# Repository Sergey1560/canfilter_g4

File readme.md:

# CAN Filter

[Схема платы](./canfilter_g4.pdf)

# Примеры кода

- [AEM2ABIT](https://github.com/Sergey1560/canfilter_aem2abit) конвертирует сообщения от ШДК AEM в формат ADLM ABIT
- [SOCKET_CAN](https://github.com/Sergey1560/canfilter_socketcan_sw) USB адаптер для Linux с 3-мя интерфейсами CAN

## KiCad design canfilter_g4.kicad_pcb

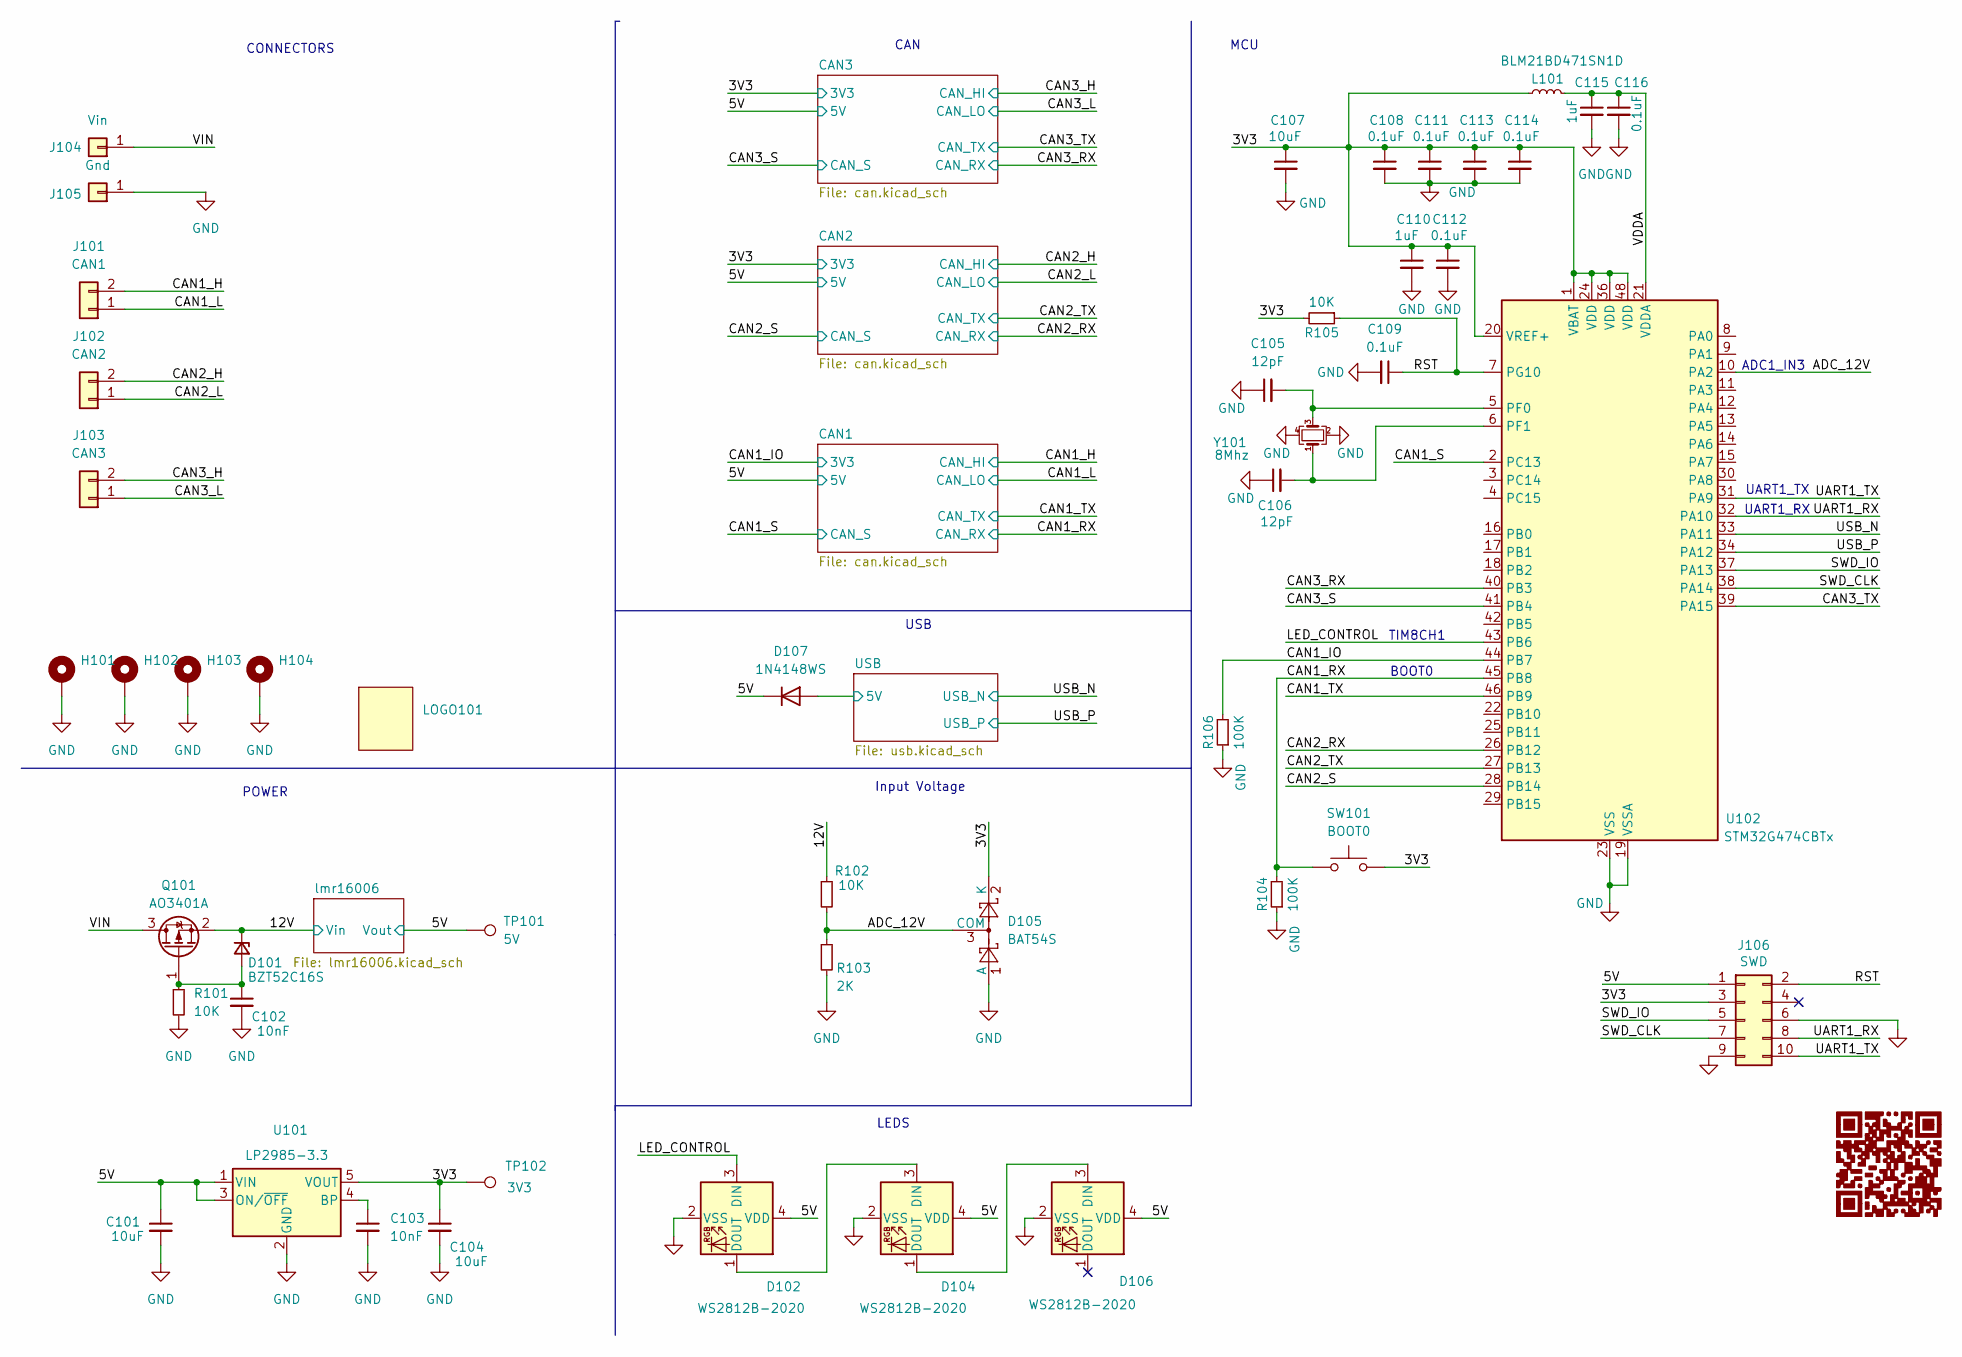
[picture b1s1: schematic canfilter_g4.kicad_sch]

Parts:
C101: 10uF; C_1206_3216Metric; LCSC C91186
C102, C103: 10nF; C_0603_1608Metric; LCSC C100042
C104: 10uF; C_1206_3216Metric; LCSC C162273
C105, C106: 12pF; C_0603_1608Metric; LCSC C519482
C107: 10uF; C_1206_3216Metric; LCSC C91606
C108, C109, C111, C113, C114, C116: 0.1uF; C_0603_1608Metric; LCSC C92490
C110: 1uF; C_0805_2012Metric; LCSC C91186
C112: 0.1uF; C_0805_2012Metric; LCSC C92490
C115: 1uF; C_0805_2012Metric; LCSC C91185
D101: BZT52C16S; D_SOD-323; LCSC C19077449
D102, D104, D106: WS2812B-2020; LED_WS2812B-2020_PLCC4_2.0x2.0mm; LCSC C965555
D105: BAT54S; SOT-23; LCSC C5805802
D107: 1N4148WS; D_SOD-323
H101, H102, H103, H104: MountingHole_3.2mm_M3_Pad_Via
J101: CAN1; PinHeader_1x02_P2.54mm_Vertical
J102: CAN2; PinHeader_1x02_P2.54mm_Vertical
J103: CAN3; PinHeader_1x02_P2.54mm_Vertical
J104: Vin; PinHeader_1x01_P2.54mm_Vertical
J105: Gnd; PinHeader_1x01_P2.54mm_Vertical
J106: SWD; PinHeader_2x05_P1.27mm_Vertical_SMD; LCSC C42372555
L101: BLM21BD471SN1D; L_0805_2012Metric; LCSC C710507
LOGO101: logo_15x9
Q101: AO3401A; SOT-23; LCSC C347476
R101, R102, R105: 10K; R_0603_1608Metric; LCSC C98220
R103: 2K; R_0603_1608Metric; LCSC C125933
R104, R106: 100K; R_0603_1608Metric; LCSC C98220
SW101: BOOT0; SW_Push_SPST_NO_Alps_SKRK
TP101: 5V; TestPoint_Pad_1.0x1.0mm
TP102: 3V3; TestPoint_Pad_1.0x1.0mm
U101: LP2985-3.3; SOT-23-5; LCSC C95414
U102: STM32G474CBTx; LQFP-48_7x7mm_P0.5mm; LCSC C730123
Y101: 8Mhz; Crystal_SMD_3225-4Pin_3.2x2.5mm; LCSC C2682775

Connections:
/3V3: C104.1, C107.1, C108.1, C110.1, C111.1, C112.1, C113.1, C114.1, D105.2 (K), J106.3, L101.1, R105.2, SW101.2, TP102.1, U101.5 (VOUT), U102.1 (VBAT), U102.20 (VREF+), U102.24 (VDD), U102.36 (VDD), U102.48 (VDD); also elsewhere on the board
/5V: C101.1, D102.4 (VDD), D104.4 (VDD), D106.4 (VDD), D107.1 (K), J106.1, TP101.1, U101.1 (VIN), U101.3 (ON/~OFF); also elsewhere on the board
/12V: D101.1 (K), Q101.2 (S), R102.1; also elsewhere on the board
/ADC_12V: D105.3 (COM), R102.2, R103.1, U102.10 (PA2)
/CAN1_H: J101.2; also elsewhere on the board
/CAN1_IO: R106.2, U102.44 (PB7); also elsewhere on the board
/CAN1_L: J101.1; also elsewhere on the board
/CAN1_RX: R104.2, SW101.1, U102.45 (PB8); also elsewhere on the board
/CAN1_S: U102.2 (PC13); also elsewhere on the board
/CAN1_TX: U102.46 (PB9); also elsewhere on the board
/CAN2_H: J102.2; also elsewhere on the board
/CAN2_L: J102.1; also elsewhere on the board
/CAN2_RX: U102.26 (PB12); also elsewhere on the board
/CAN2_S: U102.28 (PB14); also elsewhere on the board
/CAN2_TX: U102.27 (PB13); also elsewhere on the board
/CAN3_H: J103.2; also elsewhere on the board
/CAN3_L: J103.1; also elsewhere on the board
/CAN3_RX: U102.40 (PB3); also elsewhere on the board
/CAN3_S: U102.41 (PB4); also elsewhere on the board
/CAN3_TX: U102.39 (PA15); also elsewhere on the board
/LED_CONTROL: D102.3 (DIN), U102.43 (PB6)
/RST: C109.1, J106.2, R105.1, U102.7 (PG10)
/SWD_CLK: J106.7, U102.38 (PA14)
/SWD_IO: J106.5, U102.37 (PA13)
/UART1_RX: J106.8, U102.32 (PA10)
/UART1_TX: J106.10, U102.31 (PA9)
/USB/5V: D107.2 (A); also elsewhere on the board
/USB_N: U102.33 (PA11); also elsewhere on the board
/USB_P: U102.34 (PA12); also elsewhere on the board
/VDDA: C115.1, C116.1, L101.2, U102.21 (VDDA)
/VIN: J104.1, Q101.3 (D)
GND: C101.2, C102.2, C103.2, C104.2, C105.1, C106.1, C107.2, C108.2, C109.2, C110.2, C111.2, C112.2, C113.2, C114.2, C115.2, C116.2, D102.2 (VSS), D104.2 (VSS), D105.1 (A), D106.2 (VSS), H101.1, H102.1, H103.1, H104.1, J105.1, J106.6, J106.9, R101.2, R103.2, R104.1, R106.1, U101.2 (GND), U102.19 (VSSA), U102.23 (VSS), U102.35 (VSS), U102.47 (VSS), Y101.2, Y101.4; also elsewhere on the board
unnamed: C102.1, D101.2 (A), Q101.1 (G), R101.1
unnamed: D102.1 (DOUT), D104.3 (DIN)
unnamed: D104.1 (DOUT), D106.3 (DIN)
unnamed: C103.1, U101.4 (BP)
unnamed: C105.2, U102.5 (PF0), Y101.3
unnamed: C106.2, U102.6 (PF1), Y101.1

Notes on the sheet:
POWER
BOOT0
CAN
CONNECTORS
ADC1_IN3
LEDS
UART1_TX
Input Voltage
TIM8CH1
MCU
USB
UART1_RX

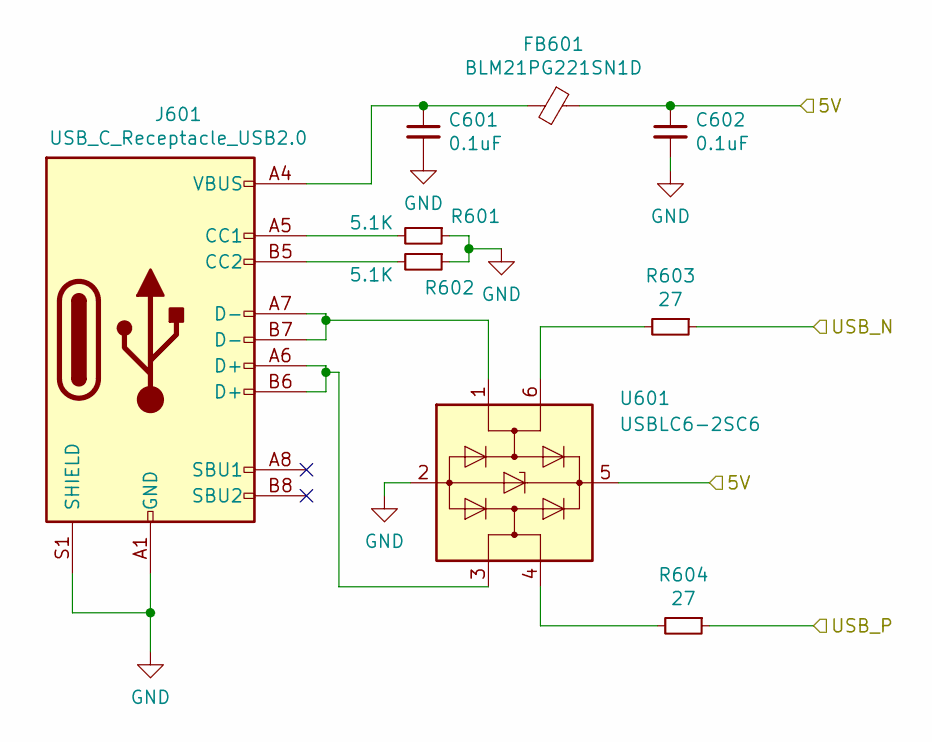
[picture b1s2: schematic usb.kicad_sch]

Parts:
C601, C602: 0.1uF; C_0603_1608Metric
FB601: BLM21PG221SN1D; L_0805_2012Metric
J601: USB_C_Receptacle_USB2.0; USB_C_Receptacle_XKB_U262-16XN-4BVC11
R601, R602: 5.1K; R_0603_1608Metric
R603, R604: 27; R_0603_1608Metric
U601: USBLC6-2SC6; SOT-23-6; LCSC C7519

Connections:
/USB/5V: C602.1, FB601.1, U601.5 (VBUS); also elsewhere on the board
/USB_N: R603.1; also elsewhere on the board
/USB_P: R604.1; also elsewhere on the board
GND: C601.2, C602.2, J601.A1 (GND), J601.A12 (GND), J601.B1 (GND), J601.B12 (GND), J601.S1 (SHIELD), R601.1, R602.1, U601.2 (GND); also elsewhere on the board
unnamed: C601.1, FB601.2, J601.A4 (VBUS), J601.A9 (VBUS), J601.B4 (VBUS), J601.B9 (VBUS)
unnamed: J601.A5 (CC1), R601.2
unnamed: J601.B5 (CC2), R602.2
unnamed: J601.A6 (D+), J601.B6 (D+), U601.3 (I/O2)
unnamed: J601.A7 (D-), J601.B7 (D-), U601.1 (I/O1)
unnamed: R603.2, U601.6 (I/O1)
unnamed: R604.2, U601.4 (I/O2)

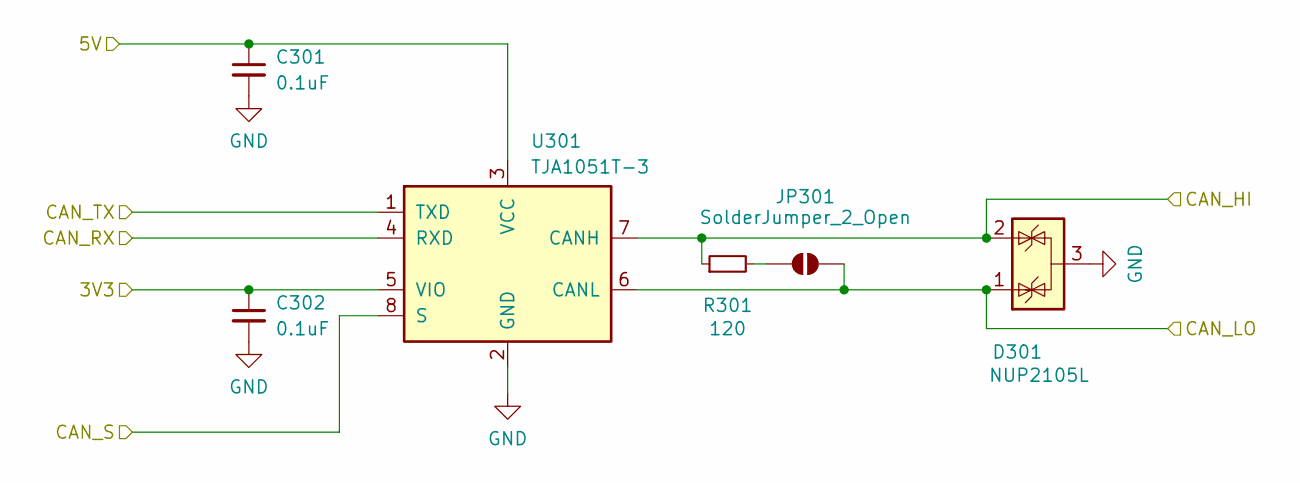
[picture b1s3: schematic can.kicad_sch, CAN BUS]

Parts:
C301, C302: 0.1uF; C_0603_1608Metric; LCSC C92490
D301: NUP2105L; SOT-23; LCSC C284104
JP301: SolderJumper_2_Open; SolderJumper-2_P1.3mm_Open_RoundedPad1.0x1.5mm
R301: 120; R_0603_1608Metric; LCSC C25196
U301: TJA1051T-3; SOIC-8_3.9x4.9mm_P1.27mm; LCSC C38695

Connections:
/5V: C301.1, U301.3 (VCC); also elsewhere on the board
/CAN1_H: D301.2 (K), R301.1, U301.7 (CANH); also elsewhere on the board
/CAN1_IO: C302.1, U301.5 (VIO); also elsewhere on the board
/CAN1_L: D301.1 (K), JP301.2 (B), U301.6 (CANL); also elsewhere on the board
/CAN1_RX: U301.4 (RXD); also elsewhere on the board
/CAN1_S: U301.8 (S); also elsewhere on the board
/CAN1_TX: U301.1 (TXD); also elsewhere on the board
GND: C301.2, C302.2, D301.3 (A), U301.2 (GND); also elsewhere on the board
unnamed: JP301.1 (A), R301.2

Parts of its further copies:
C401, C402, C501, C502: 0.1uF; C_0603_1608Metric; LCSC C92490
D401, D501: NUP2105L; SOT-23; LCSC C284104
JP401, JP501: SolderJumper_2_Open; SolderJumper-2_P1.3mm_Open_RoundedPad1.0x1.5mm
R401, R501: 120; R_0603_1608Metric; LCSC C25196
U401, U501: TJA1051T-3; SOIC-8_3.9x4.9mm_P1.27mm; LCSC C38695

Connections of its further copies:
/3V3: C402.1, C502.1, U401.5 (VIO), U501.5 (VIO); also elsewhere on the board
/5V: C401.1, C501.1, U401.3 (VCC), U501.3 (VCC); also elsewhere on the board
/CAN2_H: D401.2 (K), R401.1, U401.7 (CANH); also elsewhere on the board
/CAN2_L: D401.1 (K), JP401.2 (B), U401.6 (CANL); also elsewhere on the board
/CAN2_RX: U401.4 (RXD); also elsewhere on the board
/CAN2_S: U401.8 (S); also elsewhere on the board
/CAN2_TX: U401.1 (TXD); also elsewhere on the board
/CAN3_H: D501.2 (K), R501.1, U501.7 (CANH); also elsewhere on the board
/CAN3_L: D501.1 (K), JP501.2 (B), U501.6 (CANL); also elsewhere on the board
/CAN3_RX: U501.4 (RXD); also elsewhere on the board
/CAN3_S: U501.8 (S); also elsewhere on the board
/CAN3_TX: U501.1 (TXD); also elsewhere on the board
GND: C401.2, C402.2, C501.2, C502.2, D401.3 (A), D501.3 (A), U401.2 (GND), U501.2 (GND); also elsewhere on the board
unnamed: JP401.1 (A), R401.2
unnamed: JP501.1 (A), R501.2

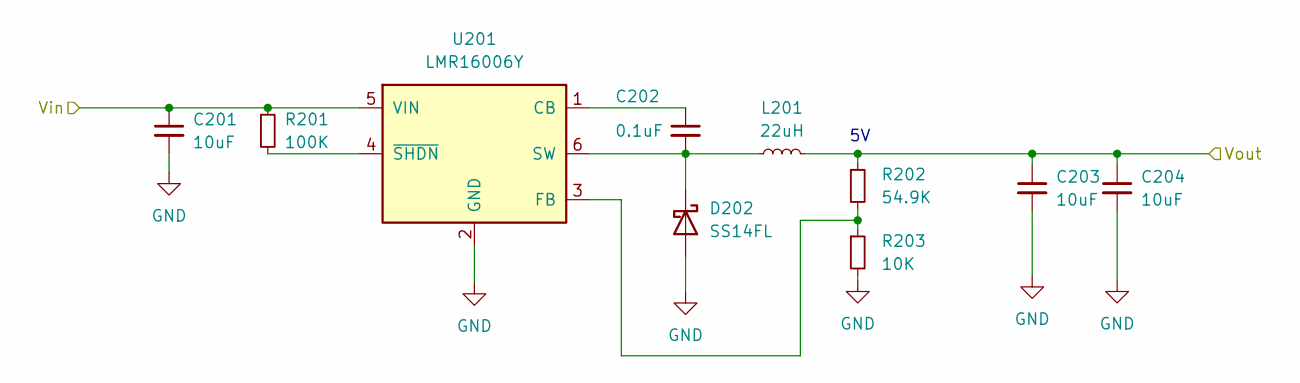
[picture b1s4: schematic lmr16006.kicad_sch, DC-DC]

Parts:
C201, C203, C204: 10uF; C_1206_3216Metric; LCSC C440198
C202: 0.1uF; C_0805_2012Metric; LCSC C14663
D202: SS14FL; D_SMA
L201: 22uH; FNR5040S220MT; LCSC C167971
R201: 100K; R_0603_1608Metric; LCSC C163504
R202: 54.9K; R_0603_1608Metric; LCSC C728593
R203: 10K; R_0603_1608Metric; LCSC C98220
U201: LMR16006Y; SOT-23-6; LCSC C290195

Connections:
/5V: C203.1, C204.1, L201.2, R202.1; also elsewhere on the board
/12V: C201.1, R201.1, U201.5 (VIN); also elsewhere on the board
GND: C201.2, C203.2, C204.2, D202.2 (A), R203.2, U201.2 (GND); also elsewhere on the board
unnamed: C202.2, D202.1 (K), L201.1, U201.6 (SW)
unnamed: C202.1, U201.1 (CB)
unnamed: R202.2, R203.1, U201.3 (FB)
unnamed: R201.2, U201.4 (~SHDN)

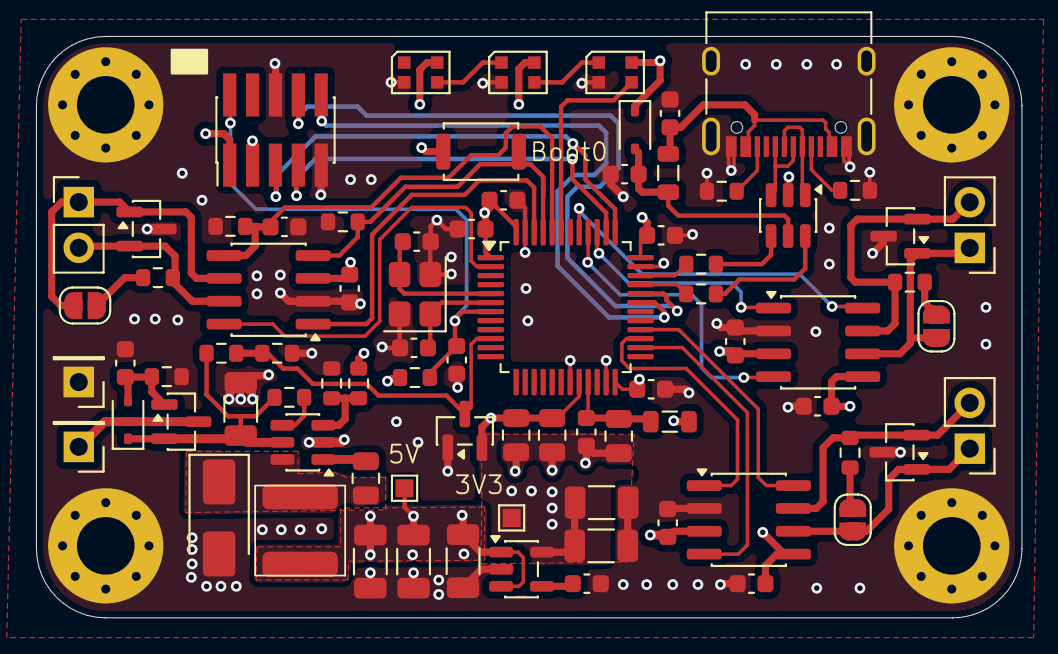
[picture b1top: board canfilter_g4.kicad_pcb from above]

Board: 4 copper layers, 54.8 x 32.3 mm, 84 parts (1 on the bottom side), 52 nets.

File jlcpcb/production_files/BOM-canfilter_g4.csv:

Comment,Designator,Footprint,LCSC,Quantity
0.1uF,"C108,C109,C111,C113,C114,C116,C301,C302,C401,C402,C501,C502,C601,C602",C_0603_1608Metric,C14663,14
0.1uF,"C112,C202",C_0805_2012Metric,C49678,2
100K,"R104,R106,R201",R_0603_1608Metric,C25803,3
10K,"R101,R102,R105,R203",R_0603_1608Metric,C25804,4
10nF,"C102,C103",C_0603_1608Metric,C57112,2
10uF,"C101,C104,C107,C201,C203,C204",C_1206_3216Metric,C13585,6
120,"R301,R401,R501",R_0603_1608Metric,C22787,3
12pF,"C105,C106",C_0603_1608Metric,C38523,2
1N4148WS,D107,D_SOD-323,C2128,1
1uF,"C110,C115",C_0805_2012Metric,C28323,2
22uH,L201,FNR5040S220MT,C167971,1
27,"R603,R604",R_0603_1608Metric,C25190,2
2K,R103,R_0603_1608Metric,C22975,1
5.1K,"R601,R602",R_0603_1608Metric,C23186,2
54.9K,R202,R_0603_1608Metric,C728593,1
8Mhz,Y101,Crystal_SMD_3225-4Pin_3.2x2.5mm,C2682775,1
AO3401A,Q101,SOT-23,C15127,1
BAT54S,D105,SOT-23,C83935,1
BLM21BD471SN1D,L101,L_0805_2012Metric,C2844596,1
BLM21PG221SN1D,FB601,L_0805_2012Metric,C85840,1
BOOT0,SW101,SW_Push_SPST_NO_Alps_SKRK,C115357,1
BZT52C16S,D101,D_SOD-323,C19077449,1
LMR16006Y,U201,SOT-23-6,C290195,1
LP2985-3.3,U101,SOT-23-5,C95414,1
NUP2105L,"D301,D401,D501",SOT-23,C14486,3
SS14FL,D202,D_SMA,C111580,1
STM32G474CBTx,U102,LQFP-48_7x7mm_P0.5mm,C730123,1
SWD,J106,PinHeader_2x05_P1.27mm_Vertical_SMD,C42372555,1
TJA1051T-3,"U301,U401,U501",SOIC-8_3.9x4.9mm_P1.27mm,C3234095,3
USBLC6-2SC6,U601,SOT-23-6,C7519,1
USB_C_Receptacle_USB2.0,J601,USB_C_Receptacle_XKB_U262-16XN-4BVC11,C319148,1
WS2812B-2020,"D102,D104,D106",LED_WS2812B-2020_PLCC4_2.0x2.0mm,C965555,3

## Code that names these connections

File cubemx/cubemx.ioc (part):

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Mcu.Name=STM32G474C(B-C-E)Tx
Mcu.Package=LQFP48
Mcu.UserName=STM32G474CBTx
PA10.Mode=Asynchronous
PA10.Signal=USART1_RX
PA11.Mode=Device
PA11.Signal=USB_DM
PA12.Mode=Device
PA12.Signal=USB_DP
PA13.Mode=Serial_Wire
PA13.Signal=SYS_JTMS-SWDIO
PA14.Mode=Serial_Wire
PA14.Signal=SYS_JTCK-SWCLK
PA15.Mode=FDCAN_Activate
PA15.Signal=FDCAN3_TX
PA2.Mode=IN3-Single-Ended
PA2.Signal=ADC1_IN3
PA9.Mode=Asynchronous
PA9.Signal=USART1_TX
PB12.Mode=FDCAN_Activate
PB12.Signal=FDCAN2_RX
PB13.Mode=FDCAN_Activate
PB13.Signal=FDCAN2_TX
PB14.GPIOParameters=GPIO_Label
PB14.GPIO_Label=CAN2_S
PB14.Signal=GPIO_Output
PB3.Mode=FDCAN_Activate
PB3.Signal=FDCAN3_RX
PB4.GPIOParameters=GPIO_Label
PB4.GPIO_Label=CAN3_S
PB4.Signal=GPIO_Output
PB6.GPIOParameters=GPIO_Label
PB6.GPIO_Label=LED_CONTROL
PB6.Signal=S_TIM8_CH1
PB7.GPIOParameters=GPIO_Label
PB7.GPIO_Label=CAN1_S
PB7.Signal=GPIO_Output
PB8-BOOT0.Mode=FDCAN_Activate
PB8-BOOT0.Signal=FDCAN1_RX
PB9.Mode=FDCAN_Activate
PB9.Signal=FDCAN1_TX
PF0-OSC_IN.Mode=HSE-External-Oscillator
PF0-OSC_IN.Signal=RCC_OSC_IN
PF1-OSC_OUT.Mode=HSE-External-Oscillator
PF1-OSC_OUT.Signal=RCC_OSC_OUT
RCC.HSE_VALUE=8000000
RCC.SYSCLKFreq_VALUE=170000000
RCC.SYSCLKSource=RCC_SYSCLKSOURCE_PLLCLK
board=custom

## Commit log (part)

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2025-12-01 Initial
2025-12-01 QR code
